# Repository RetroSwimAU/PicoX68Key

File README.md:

# PicoX68Key
An X68000 USB keyboard adaptor for 2025

See PicoX68Key.c for more information.

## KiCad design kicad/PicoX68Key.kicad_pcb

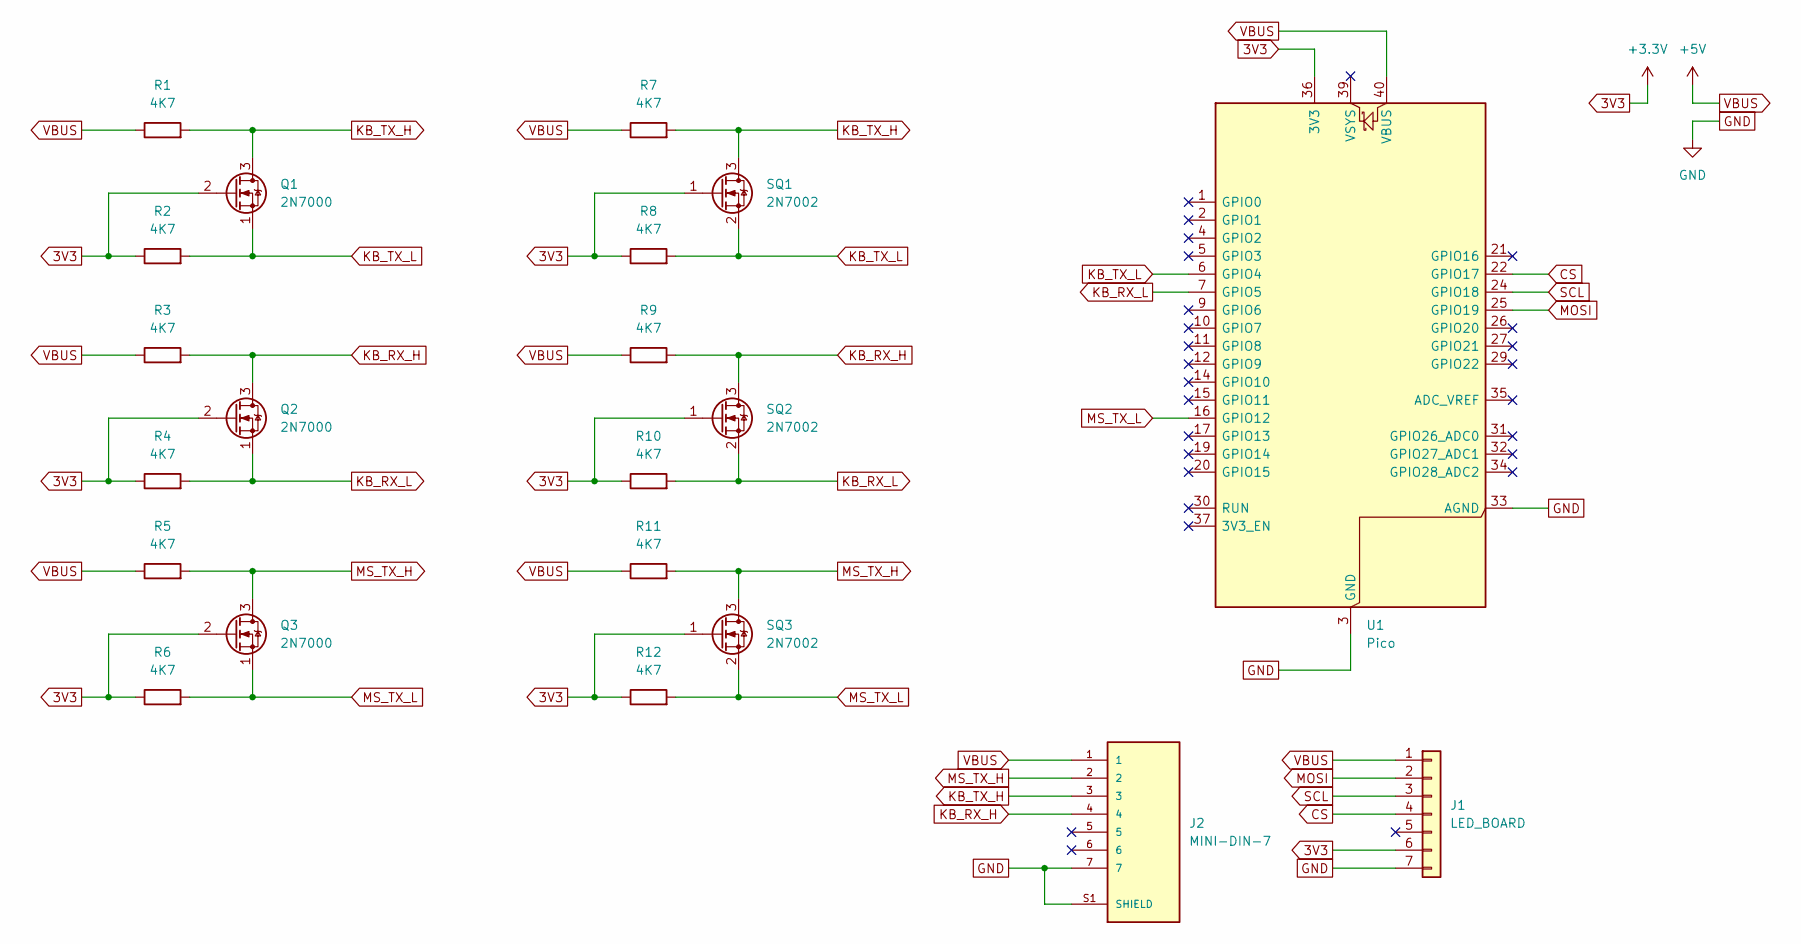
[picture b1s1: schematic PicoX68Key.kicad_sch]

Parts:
J1: LED_BOARD; PinSocket_1x07_P2.54mm_Vertical
J2: MINI-DIN-7; Mini_DIN_round_7_canned; PARTREV 02/18/2022
Q1, Q2, Q3: 2N7000; TO-92L_Inline_Wide
R1, R2, R3, R4, R5, R6: 4K7; R_Axial_DIN0309_L9.0mm_D3.2mm_P12.70mm_Horizontal
R7, R8, R9, R10, R11, R12: 4K7; R_1206_3216Metric_Pad1.30x1.75mm_HandSolder
SQ1, SQ2, SQ3: 2N7002; SOT-23
U1: Pico; RaspberryPi_Pico_Common

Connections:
3V3: J1.6, Q1.2 (G), Q2.2 (G), Q3.2 (G), R2.1, R4.1, R6.1, R8.1, R10.1, R12.1, SQ1.1 (G), SQ2.1 (G), SQ3.1 (G), U1.36 (3V3)
CS: J1.4, U1.22 (GPIO17)
GND: J1.7, J2.7, J2.S1 (SHIELD), U1.3 (GND), U1.8 (GND), U1.13 (GND), U1.18 (GND), U1.23 (GND), U1.28 (GND), U1.33 (AGND), U1.38 (GND)
KB_RX_H: J2.4, Q2.3 (D), R3.2, R9.2, SQ2.3 (D)
KB_RX_L: Q2.1 (S), R4.2, R10.2, SQ2.2 (S), U1.7 (GPIO5)
KB_TX_H: J2.3, Q1.3 (D), R1.2, R7.2, SQ1.3 (D)
KB_TX_L: Q1.1 (S), R2.2, R8.2, SQ1.2 (S), U1.6 (GPIO4)
MOSI: J1.2, U1.25 (GPIO19)
MS_TX_H: J2.2, Q3.3 (D), R5.2, R11.2, SQ3.3 (D)
MS_TX_L: Q3.1 (S), R6.2, R12.2, SQ3.2 (S), U1.16 (GPIO12)
SCL: J1.3, U1.24 (GPIO18)
VBUS: J1.1, J2.1, R1.1, R3.1, R5.1, R7.1, R9.1, R11.1, U1.40 (VBUS)

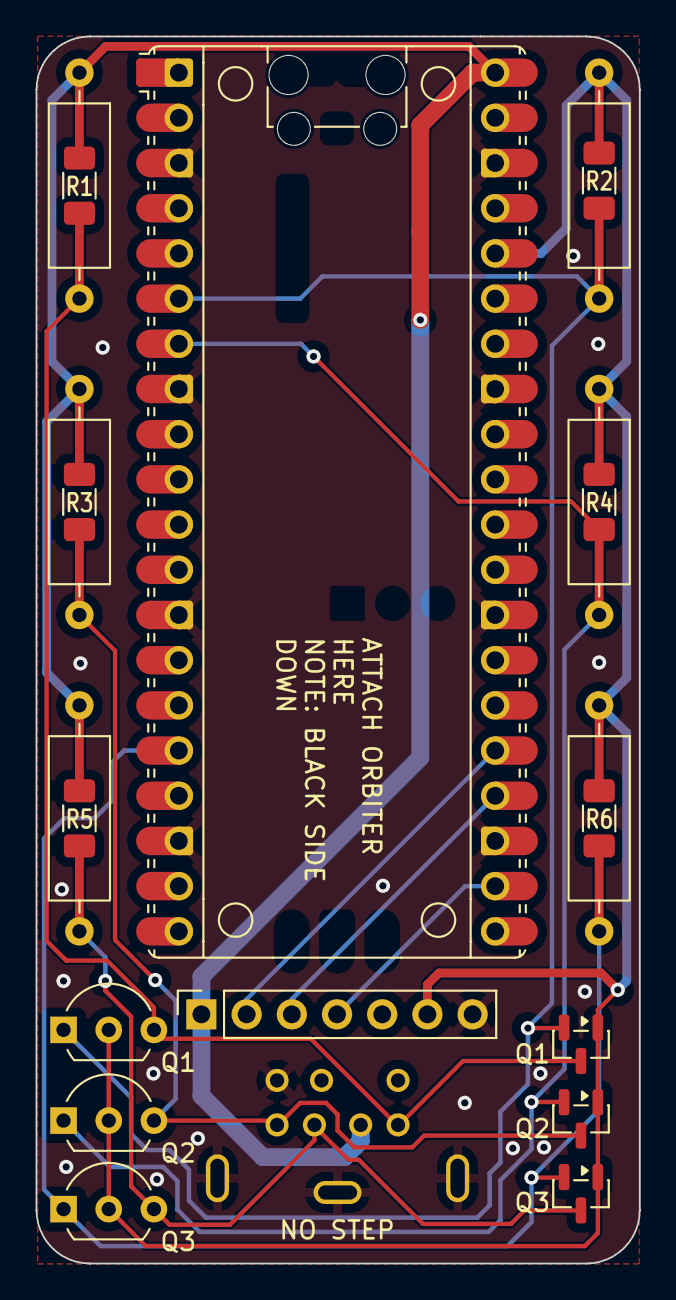
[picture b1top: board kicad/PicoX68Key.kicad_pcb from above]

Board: 2 copper layers, 33.9 x 69.0 mm, 21 parts (0 on the bottom side), 12 nets.

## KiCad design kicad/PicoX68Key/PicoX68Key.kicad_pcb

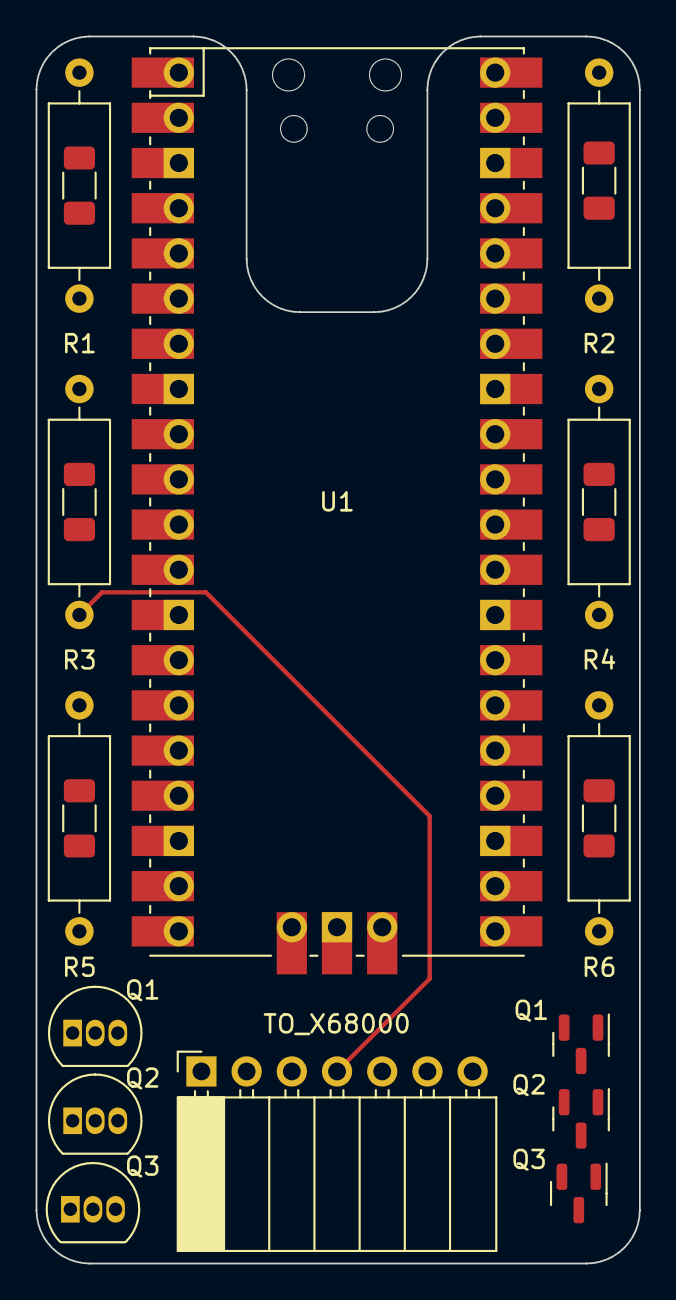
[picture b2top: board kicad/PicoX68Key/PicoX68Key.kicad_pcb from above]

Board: 2 copper layers, 33.9 x 69.0 mm, 20 parts (0 on the bottom side), 9 nets.

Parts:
J1: TO_X68000; PinSocket_1x07_P2.54mm_Horizontal
Q1, Q2#2, Q3: 2N7002; SOT-23
Q1#2, Q2, Q3#2: 2N7000; TO-92_Inline
R1, R2, R3, R4, R5, R6: 4K7; R_Axial_DIN0309_L9.0mm_D3.2mm_P12.70mm_Horizontal
R7, R8, R9, R10, R11, R12: 4K7; R_1206_3216Metric_Pad1.30x1.75mm_HandSolder
U1: Pico; RPi_Pico_SMD_TH

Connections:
3V3: Q1.1 (G), Q1#2.2 (G), Q2.2 (G), Q2#2.1 (G), Q3.1 (G), Q3#2.2 (G), R2.1, R4.1, R6.1, R8.1, R10.1, R12.1, U1.36 (3V3)
GND: J1.7, U1.3 (GND), U1.8 (GND), U1.13 (GND), U1.18 (GND), U1.23 (GND), U1.28 (GND), U1.33 (AGND), U1.38 (GND), U1.42 (GND)
KB_RX_H: J1.4, Q2.3 (D), Q2#2.3 (D), R3.2, R9.2
KB_RX_L: Q2.1 (S), Q2#2.2 (S), R4.2, R10.2, U1.7 (GPIO5)
KB_TX_H: J1.3, Q1.3 (D), Q1#2.3 (D), R1.2, R7.2
KB_TX_L: Q1.2 (S), Q1#2.1 (S), R2.2, R8.2, U1.6 (GPIO4)
MS_TX_H: J1.2, Q3.3 (D), Q3#2.3 (D), R5.2, R11.2
MS_TX_L: Q3.2 (S), Q3#2.1 (S), R6.2, R12.2, U1.16 (GPIO12)
VBUS: J1.1, R1.1, R3.1, R5.1, R7.1, R9.1, R11.1, U1.40 (VBUS)

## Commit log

2025-11-12 Goofed the ?: operators
2025-11-12 Oops, missed some Pico project files
2025-11-12 Improve .gitignore to exclude build artifacts
2025-11-13 Start PCB layout
2025-11-13 Fix KiCad directory structure
2025-11-15 Begin work PCB layout
2025-11-15 Embed 3D model, fix path
2025-11-16 Add mini-din7 connector, finish routing
2025-11-17 Don't upload lock files
2025-11-17 Layout tidy up, add flood planes
2025-11-17 New Pico footprint, change pin header to be SPI for future LED board
2025-11-17 Fix permissions
2025-11-17 Implement key repeat
2025-11-17 Got keyboard LEDs working
2025-11-17 Reflowed flood fills, first version sent to manufacture!
2025-11-19 Fix DIN footprint, board cleanup, silkscreen shenanigans
